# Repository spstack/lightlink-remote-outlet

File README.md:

# Light Link

A way to remotely link power outlets! This is an idea taken from the "Switcheroo" device that allows taking an existing switched 
power outlet and linking it wirelessly with another outlet. 

Basically, you can change the location of an outlet that is already hooked up to a switch. The device uses a simple 915MHz wireless
transceiver so there's no wifi/bluetooth involved. You just select the channel you want to control and if any device on 
that channel is powered on or off, all of the devices on that channel will follow it.

It's really useful for me in an apartment where you can't change the wiring (or just don't want to). I made about 10 of these devices to
use in multiple locations where there's a switched outlet.

|                 |                    | 
|-----------------|--------------------|
| |  |

## Board Design

The board was designed in KiCAD and manufactured by JLC PCB. The main components are a PIC microcontroller connected to an RFM69HCW
wireless transciever. There's also a relay connected to the live end of the incoming mains voltage and a small set of DIP switches for
selecting which channel to transmit on.

The power system is somewhat interesting. A 12V rail is generated through a simple switching regulator that's designed to replace 
capacitive dropper circuits (small amount of current). This rail contains some very large electrolytic capacitors that serve to store energy
and power the rest of the system for a small amount of time when mains voltage is lost. This 12V rail feeds into a second DC-DC switching regulator that powers
the digital electronics. If the 12V rail drops below a threshold, a signal is sent to the PIC to transmit the "power down" command
to all other LightLinks on it's channel.

Schematic Sheet 1 | Schematic Sheet 2 
|-----------------|--------------------|
||  |

Board Layout Front | Board Layout Back 
|-----------------|--------------------|
| |  |

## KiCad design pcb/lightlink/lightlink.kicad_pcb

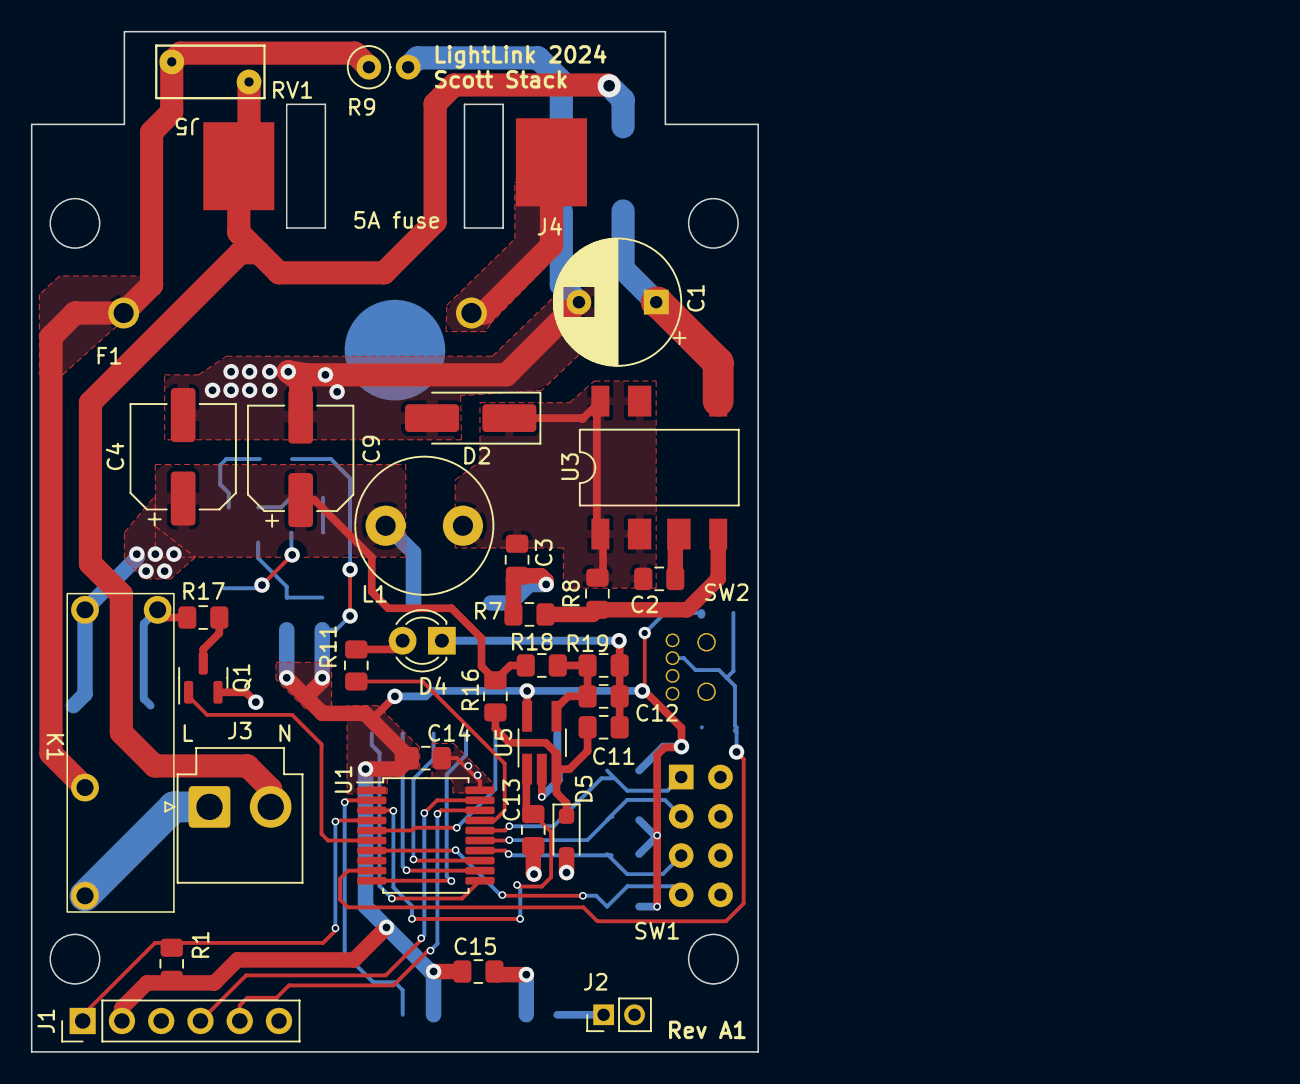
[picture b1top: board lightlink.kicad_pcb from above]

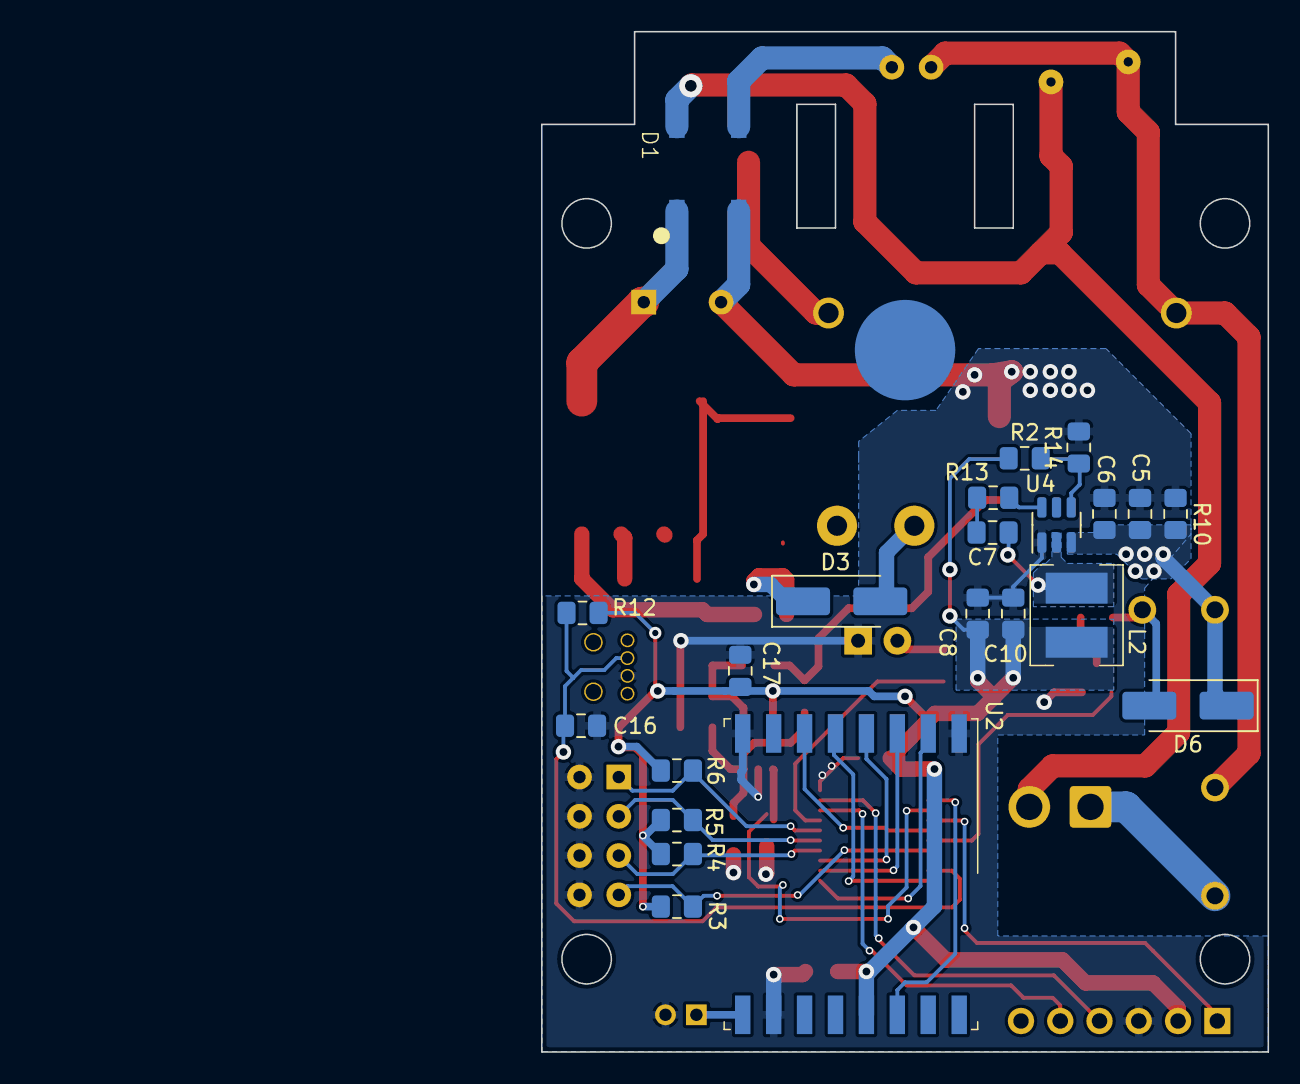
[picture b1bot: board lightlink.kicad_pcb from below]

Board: 2 copper layers, 80.0 x 66.0 mm, 59 parts (22 on the bottom side), 40 nets.

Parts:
C1: 4.7uF; CP_Radial_D8.0mm_P5.00mm
C2: 100nF; C_0805_2012Metric_Pad1.18x1.45mm_HandSolder
C3, C5: 10uF; C_0805_2012Metric_Pad1.18x1.45mm_HandSolder
C4, C9: 100uF; CP_Elec_6.3x7.7
C6, C7, C11, C12, C13, C14, C15, C16, C17: 0.1uF; C_0805_2012Metric_Pad1.18x1.45mm_HandSolder
C8, C10: 22uF; C_0805_2012Metric_Pad1.18x1.45mm_HandSolder
D1: D_Bridge_+A-A; SOPA-4
D2: D_SMA_Handsoldering
D3, D6: S1J-13-F; D_SMA_Handsoldering
D4: RED LED; LED_D3.0mm
D5: 2.7V; D_SOD-323_HandSoldering
F1: Fuse; fuseholder_20x5mm_keystone_4628
J1: PIC Programming Header; PinHeader_1x06_P2.54mm_Vertical
J2: Wire Antenna; PinHeader_1x02_P2.00mm_Vertical
J3: Conn_WallSocket; JST_VH_B2P-VH-B_1x02_P3.96mm_Vertical
J4, J5: Conn_01x01_Socket; conn_harwin_S1941-46R
K1: Relay_SPST-NO; relay_SPST_NO_panasonic_ALDP112W
L1: 1mH; L_Radial_D8.7mm_P5.00mm_Fastron_07HCP
L2: 4.7uH; L_Bourns_SRN5040
Q1: Q_NMOS_DGS; SOT-23_FDV301
R1, R3, R4, R5, R6, R12, R14: 10k; C_0805_2012Metric_Pad1.18x1.45mm_HandSolder
R2: 31.6k; C_0805_2012Metric_Pad1.18x1.45mm_HandSolder
R7: 13k; C_0805_2012Metric_Pad1.18x1.45mm_HandSolder
R8: 2.05k; C_0805_2012Metric_Pad1.18x1.45mm_HandSolder
R9: 20; R_Axial_DIN0207_L6.3mm_D2.5mm_P2.54mm_Vertical
R10: 3.3k; C_0805_2012Metric_Pad1.18x1.45mm_HandSolder
R11: 600; C_0805_2012Metric_Pad1.18x1.45mm_HandSolder
R13: 30; C_0805_2012Metric_Pad1.18x1.45mm_HandSolder
R16: 1k; C_0805_2012Metric_Pad1.18x1.45mm_HandSolder
R17: 0; C_0805_2012Metric_Pad1.18x1.45mm_HandSolder
R18: 102k; C_0805_2012Metric_Pad1.18x1.45mm_HandSolder
R19: 34k; C_0805_2012Metric_Pad1.18x1.45mm_HandSolder
RV1: Varistor; RV_Disc_D7mm_W3.4mm_P5mm
SW1: SW_DIP_x04; DIP-8_SW_Horiz_Werth
SW2: SW_MEC_5G_2LED; switch_right_angle_228DD1S1AAFAMSC
U1: PIC16F18126; SSOP-20_5.3x7.2mm_P0.65mm
U2: RFM69HCW; HOPERF_RFM69HW
U3: LNK304G; PowerIntegrations_SMD-8B
U4: TPS56339DDC; SOT-23-6
U5: TLV3201; TSOT-23-5_HandSoldering

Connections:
+3.3V: C8.1, C10.1, C14.2, C15.2, C17.2, J1.2, L2.2, R1.1, R2.1, R3.1, R4.1, R5.1, R6.1, R12.1, U1.1 (VDD), U2.13 (3.3V), U5.5 (V+)
+12V: C4.1, C5.1, C6.1, C9.1, D3.2 (A), D6.1 (K), K1.A1, L1.2, R10.1, R16.1, R18.1, U4.3 (VIN)
/microcontroller_logic/BUTTON_IN: C16.2, R12.2, SW2.1 (S1), U1.9 (RC7)
/microcontroller_logic/CHAN_SEL0: R6.2, SW1.1, U1.16 (RC0)
/microcontroller_logic/CHAN_SEL1: R5.2, SW1.2, U1.15 (RC1)
/microcontroller_logic/CHAN_SEL2: R4.2, SW1.3, U1.14 (RC2)
/microcontroller_logic/CHAN_SEL3: R3.2, SW1.4, U1.7 (RC3)
/microcontroller_logic/DIAG_LED: R11.1, U1.17 (RA2)
/microcontroller_logic/ICSPCLK: J1.5, U1.18 (RA1/ICSPCLK)
/microcontroller_logic/ICSPDAT: J1.4, U1.19 (RA0/ICSPDAT)
/microcontroller_logic/LOAD_SW0: Q1.2 (G), U1.6 (RC4)
/microcontroller_logic/RF_ANT: J2.1, U2.9 (ANT)
/microcontroller_logic/RF_INT: U1.2 (RA5), U2.14 (DIO0)
/microcontroller_logic/RF_RESET: U1.5 (RC5), U2.6 (RESET)
/microcontroller_logic/SPI_CLK: U1.13 (RB4), U2.4 (SCK)
/microcontroller_logic/SPI_CS: U1.10 (RB7), U2.5 (NSS)
/microcontroller_logic/SPI_MISO: U1.11 (RB6), U2.2 (MISO)
/microcontroller_logic/SPI_MOSI: U1.12 (RB5), U2.3 (MOSI)
/microcontroller_logic/VPP: J1.1, R1.2, U1.4 (RA3/~MCLR/VPP)
/power/3v3_FB: R2.2, R14.1, U4.4 (FB)
/power/3v3_SW: C7.2, L2.1, U4.2 (SW)
/power/12V_FB: R7.1, R8.1, U3.4 (FB)
/power/12V_FB_DIODE: C3.1, D3.1 (K), R7.2
/power/12V_SW: C2.2, C3.2, D2.1 (K), L1.1, R8.2, U3.1 (S), U3.2 (S), U3.7 (S), U3.8 (S)
/power/LNK_IN: C1.1, D1.1 (+), U3.5 (D)
/power/PLI_SENSE: C12.2, R18.2, R19.1, U5.4 (-)
/power/PLI_VREF: C11.2, D5.1 (K), R16.2, U5.3 (+)
/power/live_fbr_in: D1.4, R9.2
GND: C1.2, C4.2, C5.2, C6.2, C8.2, C9.2, C10.2, C11.1, C12.1, C13.1, C14.1, C15.1, C16.1, C17.1, D1.3 (-), D2.2 (A), D4.1 (K), D5.2 (A), J1.3, J2.2, Q1.3 (S), R10.2, R14.2, R19.2, SW1.5, SW1.6, SW1.7, SW1.8, SW2.4 (S2), U1.20 (VSS), U2.1 (GND), U2.8 (GND), U2.10 (GND), U4.1 (GND), U5.2 (V-)
LIVE_IN: F1.1, J4.1
LIVE_IN_FUSED: F1.2, K1.13, R9.1, RV1.1
LIVE_OUT: J3.1 (AC_P), K1.14
NEUTRAL_IN: D1.2, J3.2 (AC_N), J5.1, RV1.2
unnamed: C7.1, R13.2
unnamed: D4.2 (A), R11.2
unnamed: D6.2 (A), K1.A2, R17.1
unnamed: Q1.1 (D), R17.2
unnamed: C2.1, U3.3 (BP)
unnamed: R13.1, U4.6 (BOOT)
POWER_LOSS_INT: C13.2, U1.3 (RA4), U5.1

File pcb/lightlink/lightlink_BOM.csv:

"Source:","C:\Users\Scott\Dropbox\my documents\Projects_and_Misc_Tech\1_PROJECTS\RF_OutletRemote\RemoteOutlet\RemoteOutlet.kicad_sch"
"Date:","1/25/2024 11:15:09 PM"
"Tool:","Eeschema 7.0.8"
"Generator:","C:\Program Files\KiCad\7.0\bin\scripting\plugins/bom_csv_grouped_by_value.py"
"Component Count:","58"

"Collated Components:"

"Item","Qty","Reference(s)","Value","LibPart","Footprint","Datasheet","DNP","ForwardVoltageDrop","PN","Part","Sim.Device","Sim.Library","Sim.Name","Sim.Params","Sim.Pins","Voltage"
="1","1","C1","4.7uF","Device:C_Polarized_US","Capacitor_THT:CP_Radial_D8.0mm_P5.00mm","~","","","","","","","","","",""
="2","1","C2","100nF","Device:C_Small","Capacitor_SMD:C_0805_2012Metric_Pad1.18x1.45mm_HandSolder","~","","","","","","","","","",""
="3","2","C3, C5","10uF","Device:C_Polarized_US","Capacitor_SMD:C_1206_3216Metric_Pad1.33x1.80mm_HandSolder","~","","","","","","","","","","35V"
="4","2","C4, C9","100uF","Device:C_Polarized_US","Capacitor_SMD:CP_Elec_6.3x7.7","~","","","","","","","","","","35V"
="5","1","C6","0.1uF","Device:C_Polarized_US","Capacitor_SMD:C_0805_2012Metric_Pad1.18x1.45mm_HandSolder","~","","","","","","","","","",""
="6","7","C7, C11, C12, C13, C14, C15, C16","0.1uF","Device:C_Small","Capacitor_SMD:C_0805_2012Metric_Pad1.18x1.45mm_HandSolder","~","","","","","","","","","",""
="7","2","C8, C10","22uF","Device:C_Polarized_US","Capacitor_SMD:C_0805_2012Metric_Pad1.18x1.45mm_HandSolder","~","","","","","","","","","",""
="8","1","D1","D_Bridge_+A-A","Device:D_Bridge_+A-A","q_packages_sps:SOPA-4","~","","","","","","","","","",""
="9","1","D2","~","Device:D","Diode_SMD:D_SMA_Handsoldering","~","","","","","D","","","","1=K 2=A",""
="10","2","D3, D6","S1J-13-F","Device:D","Diode_SMD:D_SMA_Handsoldering","~","","","","","D","","","","1=K 2=A",""
="11","1","D4","RED LED","Device:LED","LED_THT:LED_D3.0mm","~","","1.8V","","HLMP1700","","","","","",""
="12","1","D5","2.7V","Device:D_Zener","Diode_SMD:D_SOD-323_HandSoldering","https://www.onsemi.com/pdf/datasheet/mm3z9v1b-d.pdf","","","MM3Z2V7B","","","","","","",""
="13","1","F1","Fuse","Device:Fuse","fuse_sps:fuseholder_20x5mm_keystone_4628","~","","","","","","","","","",""
"14","1","J1","PIC Programming Header","Connector:Conn_01x06_Socket","Connector_PinHeader_2.54mm:PinHeader_1x06_P2.54mm_Vertical","~","","","","","","","","","",""
"15","1","J2","Wire Antenna","Connector:Conn_01x02_Socket","Connector_PinHeader_2.00mm:PinHeader_1x02_P2.00mm_Vertical","~","","","","","","","","","",""
="16","1","J3","Conn_WallSocket","Connector:Conn_WallSocket","Connector_JST:JST_VH_B2P-VH-B_1x02_P3.96mm_Vertical","~","","","","","","","","","",""
="17","2","J4, J5","Conn_01x01_Socket","Connector:Conn_01x01_Socket","connectors_sps:conn_harwin_S1941-46R","~","","","","","","","","","",""
="18","1","K1","Relay_SPST-NO","Relay:Relay_SPST-NO","relays_sps:relay_SPST_NO_panasonic_ALDP112W","~","","","","","","","","","",""
="19","1","L1","1mH","Device:L","Inductor_THT:L_Radial_D8.7mm_P5.00mm_Fastron_07HCP","~","","","","","","","","","",""
="20","1","L2","4.7uH","Device:L","inductors_sps:L_Bourns_SRN5040","~","","","SRN5040-4R7M","","","","","","",""
="21","1","Q1","Q_NMOS_DGS","Device:Q_NMOS_DGS","q_packages_sps:SOT-23_FDV301","~","","","","","","","","","",""
="22","7","R1, R3, R4, R5, R6, R12, R14","10k","Device:R_US","Capacitor_SMD:C_0805_2012Metric_Pad1.18x1.45mm_HandSolder","~","","","","","","","","","",""
="23","1","R7","13k","Device:R_US","Capacitor_SMD:C_0805_2012Metric_Pad1.18x1.45mm_HandSolder","~","","","","","","","","","",""
="24","1","R8","2.05k","Device:R_US","Capacitor_SMD:C_0805_2012Metric_Pad1.18x1.45mm_HandSolder","~","","","","","","","","","",""
="25","1","R9","10 - Fusible","Device:R_US","Resistor_THT:R_Axial_DIN0207_L6.3mm_D2.5mm_P2.54mm_Vertical","~","","","","","","","","","",""
="26","1","R10","3.3k","Device:R_US","Capacitor_SMD:C_0805_2012Metric_Pad1.18x1.45mm_HandSolder","~","","","","","","","","","",""
="27","1","R11","600","Device:R_US","Capacitor_SMD:C_0805_2012Metric_Pad1.18x1.45mm_HandSolder","~","","","","","","","","","",""
="28","1","R13","30","Device:R_Small_US","Capacitor_SMD:C_0805_2012Metric_Pad1.18x1.45mm_HandSolder","~","","","","","","","","","",""
="29","1","R15","31.6k","Device:R_US","Capacitor_SMD:C_0805_2012Metric_Pad1.18x1.45mm_HandSolder","~","","","","","","","","","",""
="30","1","R16","1k","Device:R_US","Capacitor_SMD:C_0805_2012Metric_Pad1.18x1.45mm_HandSolder","~","","","","","","","","","",""
="31","1","R17","0","Device:R_US","Capacitor_SMD:C_0805_2012Metric_Pad1.18x1.45mm_HandSolder","~","","","","","","","","","",""
="32","1","R18","102k","Device:R_US","Capacitor_SMD:C_0805_2012Metric_Pad1.18x1.45mm_HandSolder","~","","","","","","","","","",""
="33","1","R19","34k","Device:R_US","Capacitor_SMD:C_0805_2012Metric_Pad1.18x1.45mm_HandSolder","~","","","","","","","","","",""
"34","1","RV1","Varistor","Device:Varistor","Varistor:RV_Disc_D7mm_W3.4mm_P5mm","~","","","","","SUBCKT","${KICAD7_SYMBOL_DIR}/Simulation_SPICE.sp","kicad_builtin_varistor","threshold=1k","1=A 2=B",""
="35","1","SW1","SW_DIP_x04","Switch:SW_DIP_x04","Package_DIP:DIP-8_W7.62mm","~","","","","","","","","","",""
="36","1","SW2","SW_MEC_5G_2LED","Switch:SW_MEC_5G_2LED","switches_sps:switch_right_angle_228DD1S1AAFAMSC","http://www.apem.com/int/index.php?controller=attachment&id_a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","","","","","","","","","",""
="37","1","U1","PIC16F18126","PIC_Microcontroller_sps:PIC16F18126","Package_SO:SSOP-20_5.3x7.2mm_P0.65mm","https://ww1.microchip.com/downloads/aemDocuments/documents/M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","","","","","","","","","",""
="38","1","U2","RFM69HCW","RF_Module:RFM69HCW","RF_Module:HOPERF_RFM69HW","https://www.hoperf.com/data/upload/portal/20181127/5bfcb8284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","","","","","","","","","",""
="39","1","U3","LNK304G","Regulator_Switching:LNK304G","Package_DIP:PowerIntegrations_SMD-8B","http://www.powerint.com/sites/default/files/product-docs/lnk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","","","","","","","","","",""
"40","1","U4","TPS56339DDC","Regulator_Switching:TPS56339DDC","Package_TO_SOT_SMD:SOT-23-6","https://www.ti.com/lit/ds/symlink/tps56339.pdf","","","","","","","","","",""
"41","1","U5","TLV3201","comparators_sps:TLV3201","Package_TO_SOT_SMD:TSOT-23-5_HandSoldering","","","","","","","","","","",""

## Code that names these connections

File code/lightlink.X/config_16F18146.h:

/**
 * @brief Configuration header for the PIC16F18146 microcontroller
 * @author Scott Stack
*/
#ifndef CONFIG_18146_H
#define CONFIG_18146_H

#include <xc.h>


//========================PIN ASSIGNMENTS ==========================
#define DEBUG_LED_TRIS TRISAbits.TRISA2
#define DEBUG_LED_PIN LATAbits.LATA2

#define RF_CS_TRIS TRISBbits.TRISB7
#define RF_CS_PIN LATBbits.LATB7

#define RF_RESET_TRIS TRISCbits.TRISC5
#define RF_RESET_PIN LATCbits.LATC5

#define RF_INT_TRIS TRISAbits.TRISA5
#define RF_INT_PIN PORTAbits.RA5
// #define RF_INT_IOC IOCAPbits.IOCAP5

#define SPI_MOSI_TRIS TRISBbits.TRISB5
#define SPI_MISO_TRIS TRISBbits.TRISB6
#define SPI_CLK_TRIS TRISBbits.TRISB4

#define BUTTON_TRIS TRISCbits.TRISC7
#define BUTTON_PIN PORTCbits.RC7

#define LOAD0_TRIS TRISCbits.TRISC4
#define LOAD0_PIN LATCbits.LATC4
    
#define PLI_PIN PORTAbits.RA4
#define PLI_IOC_EN IOCAPbits.IOCAP4 // enable only positive edge for trigger
#define PLI_INT_FLAG IOCAFbits.IOCAF4

#define CHAN_SEL0_TRIS TRISCbits.TRISC0
#define CHAN_SEL0_PIN PORTCbits.RC0
#define CHAN_SEL1_TRIS TRISCbits.TRISC1
#define CHAN_SEL1_PIN PORTCbits.RC1
#define CHAN_SEL2_TRIS TRISCbits.TRISC2
#define CHAN_SEL2_PIN PORTCbits.RC2
#define CHAN_SEL3_TRIS TRISCbits.TRISC3
#define CHAN_SEL3_PIN PORTCbits.RC3

    
//========================== DEFINITIONS ===============================
#define TIMER_INIT_VALUE_1MS 131 //value that timer reg needs to be set to to interrupt every 1ms

// PPS Defines for inputs
#define PPS_PORTA       (0x00)
#define PPS_PORTB       (0x08)
#define PPS_PORTC       (0x10)

#define PPS_SDO1        (0x1C) // Serial data out ID for PPS output mapping
#define PPS_SCK1        (0x1B) // serial clock out ID for PPS output
#define PPS_UART_TX1    (0x13) // UART1 Transmit


void initialize_peripherals(void);
void init_oscillator(void);
void enable_interrupts(void);
void disable_interrupts(void);
void enable_pli_int(void);
void disable_pli_int(void);
void init_GPIOs(void);
void init_SPI(void);
void init_UART(void);
void init_timers(void);

// Random number generation 
int16_t rand_sample_adc(void);
void rand_lfsr_seed(uint16_t seed);
int16_t rand_lfsr16(void);

// Critical section
void enter_critical_section(void);
void exit_critical_section(void);







#endif // CONFIG_18146_H
 

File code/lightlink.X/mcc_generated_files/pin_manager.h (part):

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#define PULL_UP_DISABLED     0

// get/set BUTTON_INPUT aliases
#define BUTTON_INPUT_PORT               PORTAbits.RA0
#define BUTTON_INPUT_GetValue()           PORTAbits.RA0

// get/set nIRQ aliases
#define nIRQ_PORT               PORTAbits.RA1
#define nIRQ_GetValue()           PORTAbits.RA1

// get/set IO_RA4 aliases
#define IO_RA4_TRIS               TRISAbits.TRISA4
#define IO_RA4_LAT                LATAbits.LATA4
#define IO_RA4_PORT               PORTAbits.RA4
#define IO_RA4_WPU                WPUAbits.WPUA4
#define IO_RA4_ANS                ANSELAbits.ANSA4
#define IO_RA4_SetHigh()            do { LATAbits.LATA4 = 1; } while(0)
#define IO_RA4_SetLow()             do { LATAbits.LATA4 = 0; } while(0)
#define IO_RA4_Toggle()             do { LATAbits.LATA4 = ~LATAbits.LATA4; } while(0)
#define IO_RA4_GetValue()           PORTAbits.RA4
#define IO_RA4_SetDigitalInput()    do { TRISAbits.TRISA4 = 1; } while(0)
#define IO_RA4_SetDigitalOutput()   do { TRISAbits.TRISA4 = 0; } while(0)
#define IO_RA4_SetPullup()      do { WPUAbits.WPUA4 = 1; } while(0)
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// get/set LOAD_SWITCH aliases
#define LOAD_SWITCH_TRIS               TRISAbits.TRISA5
#define LOAD_SWITCH_LAT                LATAbits.LATA5
#define LOAD_SWITCH_PORT               PORTAbits.RA5
#define LOAD_SWITCH_WPU                WPUAbits.WPUA5
#define LOAD_SWITCH_SetHigh()            do { LATAbits.LATA5 = 1; } while(0)
#define LOAD_SWITCH_SetLow()             do { LATAbits.LATA5 = 0; } while(0)
#define LOAD_SWITCH_Toggle()             do { LATAbits.LATA5 = ~LATAbits.LATA5; } while(0)
#define LOAD_SWITCH_GetValue()           PORTAbits.RA5
#define LOAD_SWITCH_SetDigitalInput()    do { TRISAbits.TRISA5 = 1; } while(0)
#define LOAD_SWITCH_SetDigitalOutput()   do { TRISAbits.TRISA5 = 0; } while(0)
#define LOAD_SWITCH_SetPullup()      do { WPUAbits.WPUA5 = 1; } while(0)
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// get/set SCK aliases
#define SCK_TRIS               TRISCbits.TRISC0
#define SCK_LAT                LATCbits.LATC0
#define SCK_PORT               PORTCbits.RC0
#define SCK_ANS                ANSELCbits.ANSC0
#define SCK_SetHigh()            do { LATCbits.LATC0 = 1; } while(0)
#define SCK_SetLow()             do { LATCbits.LATC0 = 0; } while(0)
#define SCK_Toggle()             do { LATCbits.LATC0 = ~LATCbits.LATC0; } while(0)
#define SCK_GetValue()           PORTCbits.RC0
#define SCK_SetDigitalInput()    do { TRISCbits.TRISC0 = 1; } while(0)
#define SCK_SetDigitalOutput()   do { TRISCbits.TRISC0 = 0; } while(0)
#define SCK_SetAnalogMode()  do { ANSELCbits.ANSC0 = 1; } while(0)
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// get/set SDI aliases
#define SDI_TRIS               TRISCbits.TRISC1
#define SDI_LAT                LATCbits.LATC1
#define SDI_PORT               PORTCbits.RC1
#define SDI_ANS                ANSELCbits.ANSC1
#define SDI_SetHigh()            do { LATCbits.LATC1 = 1; } while(0)
#define SDI_SetLow()             do { LATCbits.LATC1 = 0; } while(0)
#define SDI_Toggle()             do { LATCbits.LATC1 = ~LATCbits.LATC1; } while(0)
#define SDI_GetValue()           PORTCbits.RC1
#define SDI_SetDigitalInput()    do { TRISCbits.TRISC1 = 1; } while(0)
#define SDI_SetDigitalOutput()   do { TRISCbits.TRISC1 = 0; } while(0)
#define SDI_SetAnalogMode()  do { ANSELCbits.ANSC1 = 1; } while(0)
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// get/set SDO aliases
#define SDO_TRIS               TRISCbits.TRISC2
#define SDO_LAT                LATCbits.LATC2
#define SDO_PORT               PORTCbits.RC2
#define SDO_ANS                ANSELCbits.ANSC2
#define SDO_SetHigh()            do { LATCbits.LATC2 = 1; } while(0)
#define SDO_SetLow()             do { LATCbits.LATC2 = 0; } while(0)
#define SDO_Toggle()             do { LATCbits.LATC2 = ~LATCbits.LATC2; } while(0)
#define SDO_GetValue()           PORTCbits.RC2
#define SDO_SetDigitalInput()    do { TRISCbits.TRISC2 = 1; } while(0)
#define SDO_SetDigitalOutput()   do { TRISCbits.TRISC2 = 0; } while(0)
#define SDO_SetAnalogMode()  do { ANSELCbits.ANSC2 = 1; } while(0)
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// get/set DEBUG_LED aliases
#define DEBUG_LED_TRIS               TRISCbits.TRISC3
#define DEBUG_LED_LAT                LATCbits.LATC3
#define DEBUG_LED_PORT               PORTCbits.RC3
#define DEBUG_LED_ANS                ANSELCbits.ANSC3
#define DEBUG_LED_SetHigh()            do { LATCbits.LATC3 = 1; } while(0)
#define DEBUG_LED_SetLow()             do { LATCbits.LATC3 = 0; } while(0)
#define DEBUG_LED_Toggle()             do { LATCbits.LATC3 = ~LATCbits.LATC3; } while(0)
#define DEBUG_LED_GetValue()           PORTCbits.RC3
#define DEBUG_LED_SetDigitalInput()    do { TRISCbits.TRISC3 = 1; } while(0)
#define DEBUG_LED_SetDigitalOutput()   do { TRISCbits.TRISC3 = 0; } while(0)
#define DEBUG_LED_SetAnalogMode()  do { ANSELCbits.ANSC3 = 1; } while(0)
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#define RC4_SetHigh()    do { LATCbits.LATC4 = 1; } while(0)
#define RC4_SetLow()   do { LATCbits.LATC4 = 0; } while(0)
#define RC4_Toggle()   do { LATCbits.LATC4 = ~LATCbits.LATC4; } while(0)
#define RC4_GetValue()         PORTCbits.RC4
#define RC4_SetDigitalInput()   do { TRISCbits.TRISC4 = 1; } while(0)
#define RC4_SetDigitalOutput()  do { TRISCbits.TRISC4 = 0; } while(0)

// get/set RX_LED aliases
#define RX_LED_TRIS               TRISCbits.TRISC5
#define RX_LED_LAT                LATCbits.LATC5
#define RX_LED_PORT               PORTCbits.RC5
#define RX_LED_SetHigh()            do { LATCbits.LATC5 = 1; } while(0)
#define RX_LED_SetLow()             do { LATCbits.LATC5 = 0; } while(0)
#define RX_LED_Toggle()             do { LATCbits.LATC5 = ~LATCbits.LATC5; } while(0)
#define RX_LED_GetValue()           PORTCbits.RC5
#define RX_LED_SetDigitalInput()    do { TRISCbits.TRISC5 = 1; } while(0)
#define RX_LED_SetDigitalOutput()   do { TRISCbits.TRISC5 = 0; } while(0)

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
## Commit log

2024-01-30 Add initial version of the light link repo
    This initial commit includes the whole project that's mostly completed
    The PCB design has not yet been sent off, but PIC code has been developed
    and tested in a breadboard.
    Tried to nicely organize all components into folders, but probably should
    have done this earlier in the project for better history :)
2024-01-30 Adding Official RevA0 of the PCB design
2024-02-09 Add released gerber files and fix board problem with reversed resistors
2024-02-09 Change behavior of debug LED to show outlet power state
2024-02-26 Fix channel select and remove debug LED flash
    Also update PCB with a few fixes from assembly and test
2024-03-02 Update PCB with several fixes
    * Increase value of inrush limiting resistor
    * Update locations of button/DIP switch
    * Fix footprint for DIP switch
    * Fix footprint for full bridge rectifier
    * Change 1206 cap footprints to 0805
    * Rotate main JST connector so that it doesn't impact the plug
2024-04-03 Update PCB with couple fixes, cleanup code a bit
2024-04-03 Add a couple images of completed project
2024-04-03 Fix filename typo
2024-04-05 Disable LED blinking and cleanup logging messages a bit
2024-04-27 Move logging to new source file
2024-04-29 Refactor LED blink logic and logging a bit
2024-06-18 Fix a few corner cases that may have been causing hangs
    Observed a couple units go unresponsive after a couple weeks of
    power on time without reset. Added a few additional checks and
    improvements to code robustness to hopefully address this.
    Don't have any proof that any of these changes will help for sure,
    but they are more correct and hopefully help recover from corner
    cases.
2024-06-19 Add critical sections around timer code
    Attempt to fix a few potential issues by putting critical section
    around timer access.
    Also add some additional error codes for debug and ability to
    trap an error so it repeatedly blinks last error
2024-07-28 Fix bug that caused infinite loop in PLI interrupt
2024-07-28 Update gitignore
2024-07-28 Fix timeout values for tx and ack receipt
2024-12-03 Update the README and add pdf version of SCH

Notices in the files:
code/lightlink.X/mcc_generated_files/pin_manager.h:
Copyright (c) 2013 - 2015 released Microchip Technology Inc.  All rights reserved.
